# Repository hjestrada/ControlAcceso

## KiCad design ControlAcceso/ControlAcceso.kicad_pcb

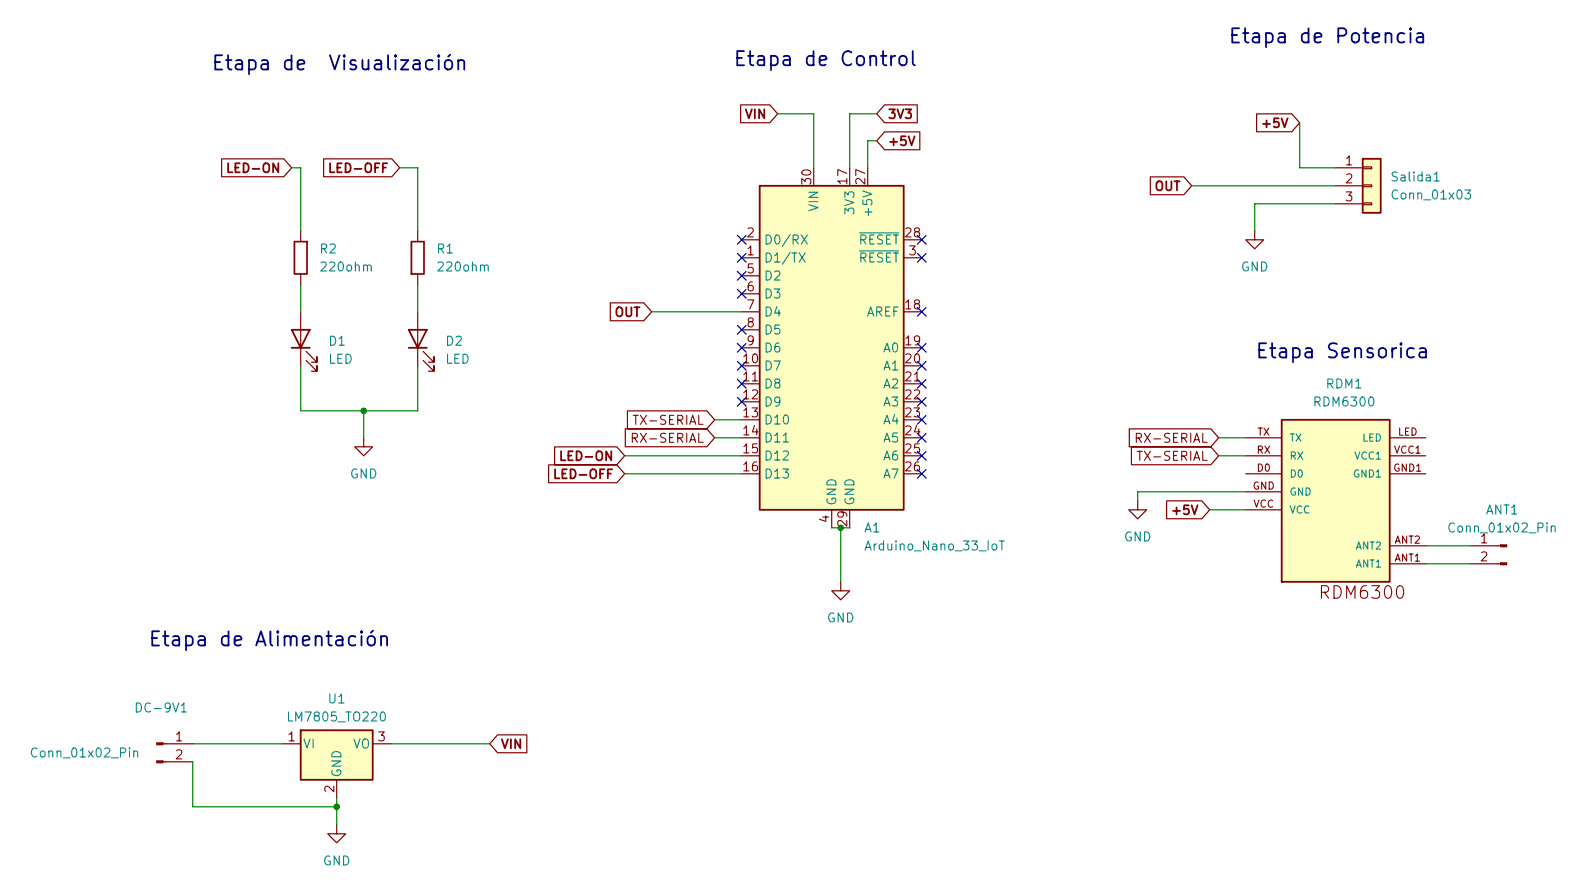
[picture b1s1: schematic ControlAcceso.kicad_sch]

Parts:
A1: Arduino_Nano_33_IoT; Arduino_Nano
ANT1: Conn_01x02_Pin; PinHeader_1x02_P2.54mm_Vertical
D1, D2: LED; LED_D5.0mm
DC-9V1: Conn_01x02_Pin; PinHeader_1x02_P2.54mm_Vertical
R1, R2: 220ohm; R_Axial_DIN0207_L6.3mm_D2.5mm_P10.16mm_Horizontal
RDM1: RDM6300
Salida1: Conn_01x03; PinHeader_1x03_P2.54mm_Vertical; Part Number 1-0301FBV0T
U1: LM7805_TO220; TO-220-3_Vertical

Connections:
3V3: A1.17 (3V3)
+5V: A1.27 (+5V), RDM1.VCC, Salida1.1
GND: A1.4 (GND), A1.29 (GND), D1.1 (K), D2.1 (K), DC-9V1.2, RDM1.GND, Salida1.3, U1.2 (GND)
LED-OFF: A1.16 (D13), R1.2
LED-ON: A1.15 (D12), R2.1
unnamed: ANT1.1, RDM1.ANT2
unnamed: ANT1.2, RDM1.ANT1
unnamed: D1.2 (A), R2.2
unnamed: D2.2 (A), R1.1
unnamed: DC-9V1.1, U1.1 (VI)
OUT: A1.7 (D4), Salida1.2
RX-SERIAL: A1.14 (D11), RDM1.TX
TX-SERIAL: A1.13 (D10), RDM1.RX
VIN: A1.30 (VIN), U1.3 (VO)

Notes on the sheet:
Etapa de Alimentación
Etapa de Control
Etapa de Visualización
Etapa de Potencia
Etapa Sensorica

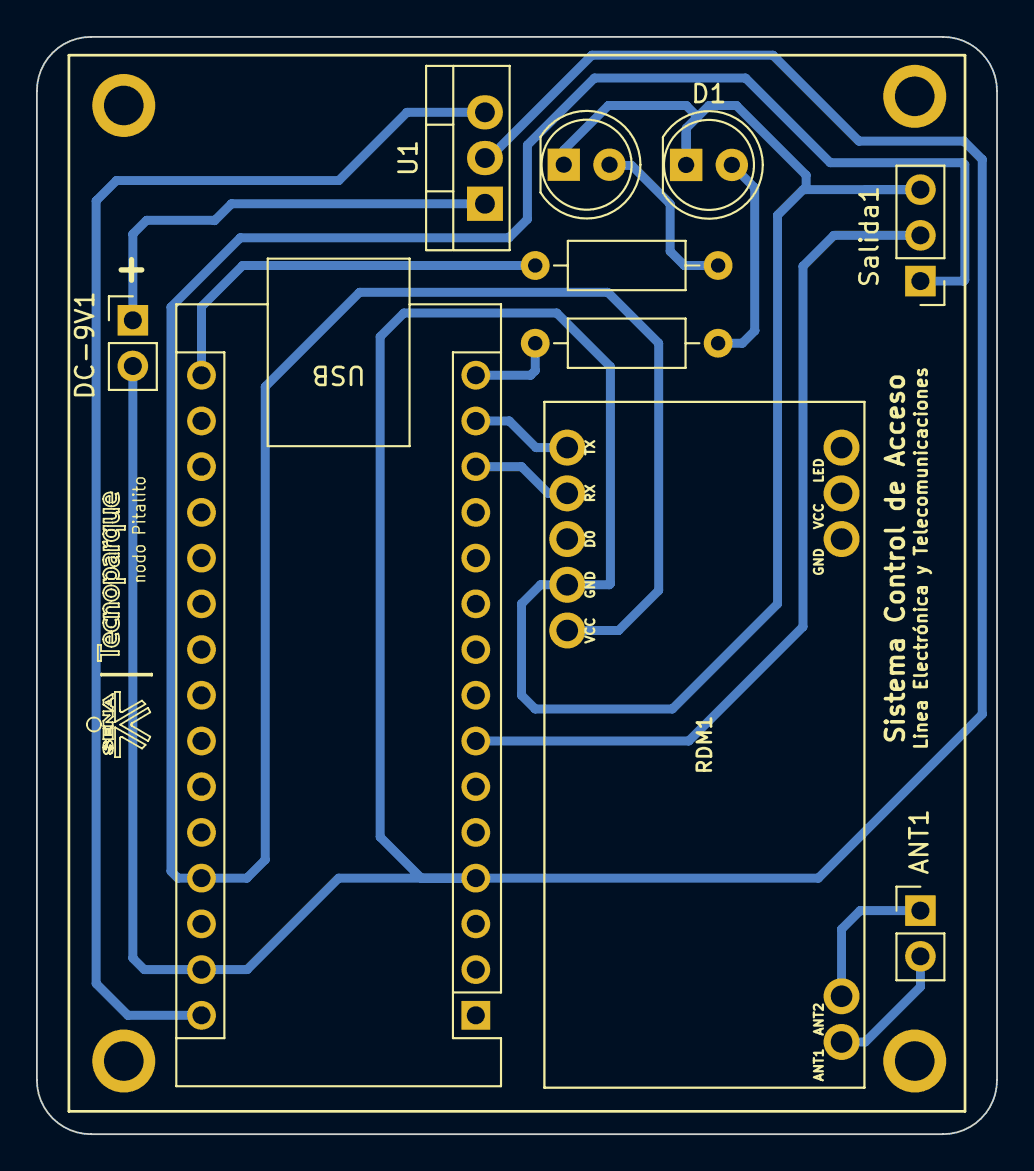
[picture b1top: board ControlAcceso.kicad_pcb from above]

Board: 2 copper layers, 53.3 x 61.0 mm, 10 parts (0 on the bottom side), 13 nets.

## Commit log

2024-02-13 PrimerCommit
2024-02-13 Cambios
2024-02-14 Ultimo
    Generación de archivos GERBER, modificacion de rutas
2024-02-14 Otros cambios
2024-02-14 cambvios
2024-02-15 Cambios Significativos
    Se quito codigo de prueba, se cambio modulo RFID y se agrego regulador 7805.
2024-02-15 Modificaciones Varias
2024-02-17 Factura PCB
2024-03-02 Muchos cambios
2024-03-02 Modificacion PCB y codigo
2024-03-04 Codigo bueno
2024-03-04 Documentacion
2024-05-01 CAMBIKOS
